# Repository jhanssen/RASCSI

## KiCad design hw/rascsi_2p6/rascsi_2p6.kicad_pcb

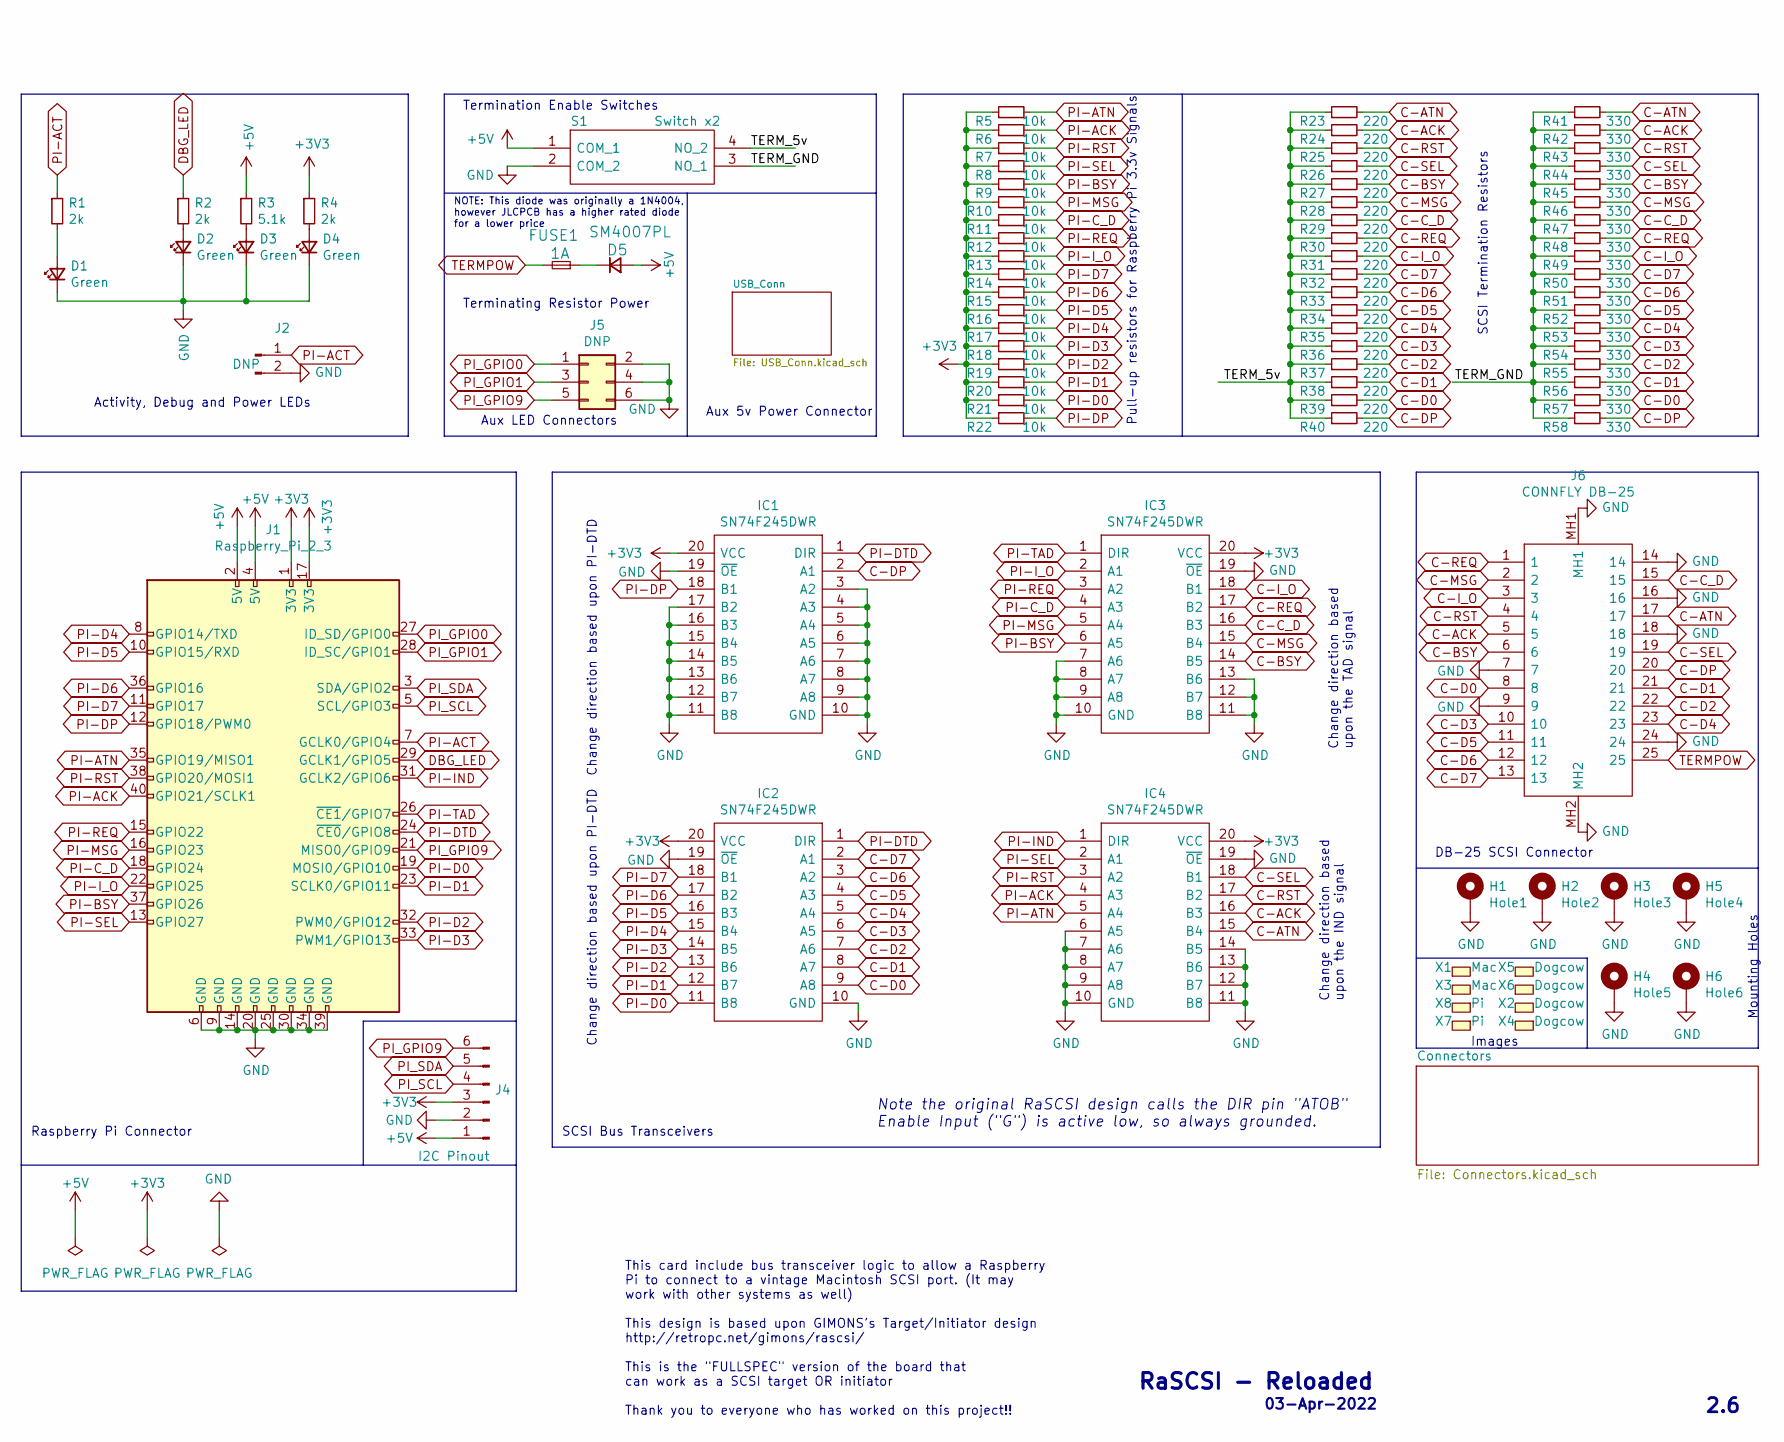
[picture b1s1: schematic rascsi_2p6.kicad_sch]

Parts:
D1, D2, D3, D4: Green; LED_0805_2012Metric; Manufacturer_Part_Number C2297; LCSC C2297
D5: SM4007PL; D_SOD-123F; Manufacturer_Part_Number SM4007PL; LCSC C64898
FUSE1: 1A; Fuse_1206_3216Metric; Manufacturer_Part_Number 12B1100B; LCSC C182974
H1: Hole1; MountingHole_2.7mm_M2.5_Pad_Via; Manufacturer_Part_Number DNP; LCSC DNP
H2: Hole2; MountingHole_2.7mm_M2.5_Pad_Via; Manufacturer_Part_Number DNP; LCSC DNP
H3: Hole3; MountingHole_2.7mm_M2.5_Pad_Via; Manufacturer_Part_Number DNP; LCSC DNP
H4: Hole5; MountingHole_2.7mm_M2.5_Pad_Via; Manufacturer_Part_Number DNP; LCSC DNP
H5: Hole4; MountingHole_2.7mm_M2.5_Pad_Via; Manufacturer_Part_Number DNP; LCSC DNP
H6: Hole6; MountingHole_2.7mm_M2.5_Pad_Via; Manufacturer_Part_Number DNP; LCSC DNP
IC1, IC2, IC3, IC4: SN74F245DWR; SOIC127P1030X265-20N; Manufacturer_Part_Number SN74F245DWR; LCSC C7165
J1: Raspberry_Pi_2_3; PinSocket_2x20_P2.54mm_Vertical; Manufacturer_Part_Number C50982; LCSC C50982
J2: DNP; PinHeader_1x02_P2.54mm_Horizontal; Manufacturer_Part_Number DNP; LCSC DNP
J4: I2C Pinout; PinSocket_1x06_P2.54mm_Vertical; Manufacturer_Part_Number C40877; LCSC C40877
J5: DNP; PinHeader_2x03_P2.54mm_Vertical; Manufacturer_Part_Number DNP; LCSC DNP
J6: CONNFLY DB-25; L717SDB25PA4CH4F; Manufacturer_Part_Number DS1037-25FNAKT74-0CC; LCSC C77838
R1, R2, R4: 2k; R_0402_1005Metric; Manufacturer_Part_Number 0402WGF2001TCE; LCSC C4109
R3: 5.1k; R_0402_1005Metric; Manufacturer_Part_Number 0402WGF5101TCE; LCSC C25905
R5, R6, R7, R8, R9, R10, R11, R12, R13, R14, R15, R16, R17, R18, R19, R20, R21, R22: 10k; R_0402_1005Metric; Manufacturer_Part_Number 0402WGF1002TCE; LCSC C25744
R23, R24, R25, R26, R27, R28, R29, R30, R31, R32, R33, R34, R35, R36, R37, R38, R39, R40: 220; R_0805_2012Metric; Manufacturer_Part_Number 0805W8F2200T5E; LCSC C17557
R41, R42, R43, R44, R45, R46, R47, R48, R49, R50, R51, R52, R53, R54, R55, R56, R57, R58: 330; R_0805_2012Metric; Manufacturer_Part_Number 0805W8F3300T5E; LCSC C17630
S1: Switch x2; SOIC127P812X230-4N; Manufacturer_Part_Number DSHP02TSGET; LCSC C40735
X1, X3: Mac; mac_happy_small; Manufacturer_Part_Number N/A; LCSC N/A
X2, X4, X5, X6: Dogcow; dogcow; Manufacturer_Part_Number N/A; LCSC N/A
X7: Pi; pi_logo; Manufacturer_Part_Number N/A; LCSC N/A
X8: Pi; scsi_logo; Manufacturer_Part_Number N/A; LCSC N/A

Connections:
+3V3: IC1.20 (VCC), IC2.20 (VCC), IC3.20 (VCC), IC4.20 (VCC), J1.1 (3V3), J1.17 (3V3), J4.3, R4.1, R5.1, R6.1, R7.1, R8.1, R9.1, R10.1, R11.1, R12.1, R13.1, R14.1, R15.1, R16.1, R17.1, R18.1, R19.1, R20.1, R21.1, R22.1
+5V: D5.2 (A), J1.2 (5V), J1.4 (5V), J4.1, R3.1, S1.1 (COM_1); also elsewhere on the board
/TERM_5v: R23.1, R24.1, R25.1, R26.1, R27.1, R28.1, R29.1, R30.1, R31.1, R32.1, R33.1, R34.1, R35.1, R36.1, R37.1, R38.1, R39.1, R40.1, S1.4 (NO_2)
/TERM_GND: R41.1, R42.1, R43.1, R44.1, R45.1, R46.1, R47.1, R48.1, R49.1, R50.1, R51.1, R52.1, R53.1, R54.1, R55.1, R56.1, R57.1, R58.1, S1.3 (NO_1)
C-ACK: IC4.16 (B3), J6.5, R24.2, R42.2; also elsewhere on the board
C-ATN: IC4.15 (B4), J6.17, R23.2, R41.2; also elsewhere on the board
C-BSY: IC3.14 (B5), J6.6, R27.2, R45.2; also elsewhere on the board
C-C_D: IC3.16 (B3), J6.15, R29.2, R47.2; also elsewhere on the board
C-D0: IC2.9 (A8), J6.8, R39.2, R57.2; also elsewhere on the board
C-D1: IC2.8 (A7), J6.21, R38.2, R56.2; also elsewhere on the board
C-D2: IC2.7 (A6), J6.22, R37.2, R55.2; also elsewhere on the board
C-D3: IC2.6 (A5), J6.10, R36.2, R54.2; also elsewhere on the board
C-D4: IC2.5 (A4), J6.23, R35.2, R53.2; also elsewhere on the board
C-D5: IC2.4 (A3), J6.11, R34.2, R52.2; also elsewhere on the board
C-D6: IC2.3 (A2), J6.12, R33.2, R51.2; also elsewhere on the board
C-D7: IC2.2 (A1), J6.13, R32.2, R50.2; also elsewhere on the board
C-DP: IC1.2 (A1), J6.20, R40.2, R58.2; also elsewhere on the board
C-I_O: IC3.18 (B1), J6.3, R31.2, R49.2; also elsewhere on the board
C-MSG: IC3.15 (B4), J6.2, R28.2, R46.2; also elsewhere on the board
C-REQ: IC3.17 (B2), J6.1, R30.2, R48.2; also elsewhere on the board
C-RST: IC4.17 (B2), J6.4, R25.2, R43.2; also elsewhere on the board
C-SEL: IC4.18 (B1), J6.19, R26.2, R44.2; also elsewhere on the board
DBG_LED: J1.29 (GCLK1/GPIO5), R2.1
GND: D1.1 (K), D2.1 (K), D3.1 (K), D4.1 (K), H1.1, H2.1, H3.1, H4.1, H5.1, H6.1, IC1.3 (A2), IC1.4 (A3), IC1.5 (A4), IC1.6 (A5), IC1.7 (A6), IC1.8 (A7), IC1.9 (A8), IC1.10 (GND), IC1.11 (B8), IC1.12 (B7), IC1.13 (B6), IC1.14 (B5), IC1.15 (B4), IC1.16 (B3), IC1.17 (B2), IC1.19 (~OE), IC2.10 (GND), IC2.19 (~OE), IC3.7 (A6), IC3.8 (A7), IC3.9 (A8), IC3.10 (GND), IC3.11 (B8), IC3.12 (B7), IC3.13 (B6), IC3.19 (~OE), IC4.6 (A5), IC4.7 (A6), IC4.8 (A7), IC4.9 (A8), IC4.10 (GND), IC4.11 (B8), IC4.12 (B7), IC4.13 (B6), IC4.14 (B5), IC4.19 (~OE), J1.6 (GND), J1.9 (GND), J1.14 (GND), J1.20 (GND), J1.25 (GND), J1.30 (GND), J1.34 (GND), J1.39 (GND), J2.2, J4.2, J5.2, J5.4, J5.6, J6.7, J6.9, J6.14, J6.16, J6.18, J6.24, J6.MH1, J6.MH2, S1.2 (COM_2); also elsewhere on the board
unnamed: D1.2 (A), R1.2
unnamed: D2.2 (A), R2.2
unnamed: D3.2 (A), R3.2
unnamed: D4.2 (A), R4.2
unnamed: D5.1 (K), FUSE1.1
PI-ACK: IC4.4 (A3), J1.40 (GPIO21/SCLK1), R6.2
PI-ACT: J1.7 (GCLK0/GPIO4), J2.1, R1.1; also elsewhere on the board
PI-ATN: IC4.5 (A4), J1.35 (GPIO19/MISO1), R5.2
PI-BSY: IC3.6 (A5), J1.37 (GPIO26), R9.2
PI-C_D: IC3.4 (A3), J1.18 (GPIO24), R11.2
PI-D0: IC2.11 (B8), J1.19 (MOSI0/GPIO10), R21.2
PI-D1: IC2.12 (B7), J1.23 (SCLK0/GPIO11), R20.2
PI-D2: IC2.13 (B6), J1.32 (PWM0/GPIO12), R19.2
PI-D3: IC2.14 (B5), J1.33 (PWM1/GPIO13), R18.2
PI-D4: IC2.15 (B4), J1.8 (GPIO14/TXD), R17.2
PI-D5: IC2.16 (B3), J1.10 (GPIO15/RXD), R16.2
PI-D6: IC2.17 (B2), J1.36 (GPIO16), R15.2
PI-D7: IC2.18 (B1), J1.11 (GPIO17), R14.2
PI-DP: IC1.18 (B1), J1.12 (GPIO18/PWM0), R22.2
PI-DTD: IC1.1 (DIR), IC2.1 (DIR), J1.24 (~CE0/GPIO8)
PI-IND: IC4.1 (DIR), J1.31 (GCLK2/GPIO6)
PI-I_O: IC3.2 (A1), J1.22 (GPIO25), R13.2
PI-MSG: IC3.5 (A4), J1.16 (GPIO23), R10.2
PI-REQ: IC3.3 (A2), J1.15 (GPIO22), R12.2
PI-RST: IC4.3 (A2), J1.38 (GPIO20/MOSI1), R7.2
PI-SEL: IC4.2 (A1), J1.13 (GPIO27), R8.2
PI-TAD: IC3.1 (DIR), J1.26 (~CE1/GPIO7)
PI_GPIO0: J1.27 (ID_SD/GPIO0), J5.1
PI_GPIO1: J1.28 (ID_SC/GPIO1), J5.3
PI_GPIO9: J1.21 (MISO0/GPIO9), J4.6, J5.5
PI_SCL: J1.5 (SCL/GPIO3), J4.4
PI_SDA: J1.3 (SDA/GPIO2), J4.5
TERMPOW: FUSE1.2, J6.25; also elsewhere on the board

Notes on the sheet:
Images
RaSCSI - Reloaded
2.6
Raspberry Pi Connector
Change direction based upon the TAD signal
Terminating Resistor Power
Mounting Holes
03-Apr-2022
DB-25 SCSI Connector
SCSI Termination Resistors
Pull-up resistors for Raspberry Pi 3.3v Signals
Change direction based upon the IND signal
NOTE: This diode was originally a 1N4004, however JLCPCB has a higher rated diode for a lower price
Change direction based upon PI-DTD
Note the original RaSCSI design calls the DIR pin "ATOB" Enable Input ("G") is active low, so always grounded.
Activity, Debug and Power LEDs
Termination Enable Switches
This card include bus transceiver logic to allow a Raspberry Pi to connect to a vintage Macintosh SCSI port. (It may work with other systems as well) This design is based upon GIMONS's Target/Initiator design http://retropc.net/gimons/rascsi/ This is the "FULLSPEC" version of the board that can wor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
Aux 5v Power Connector
SCSI Bus Transceivers
Aux LED Connectors

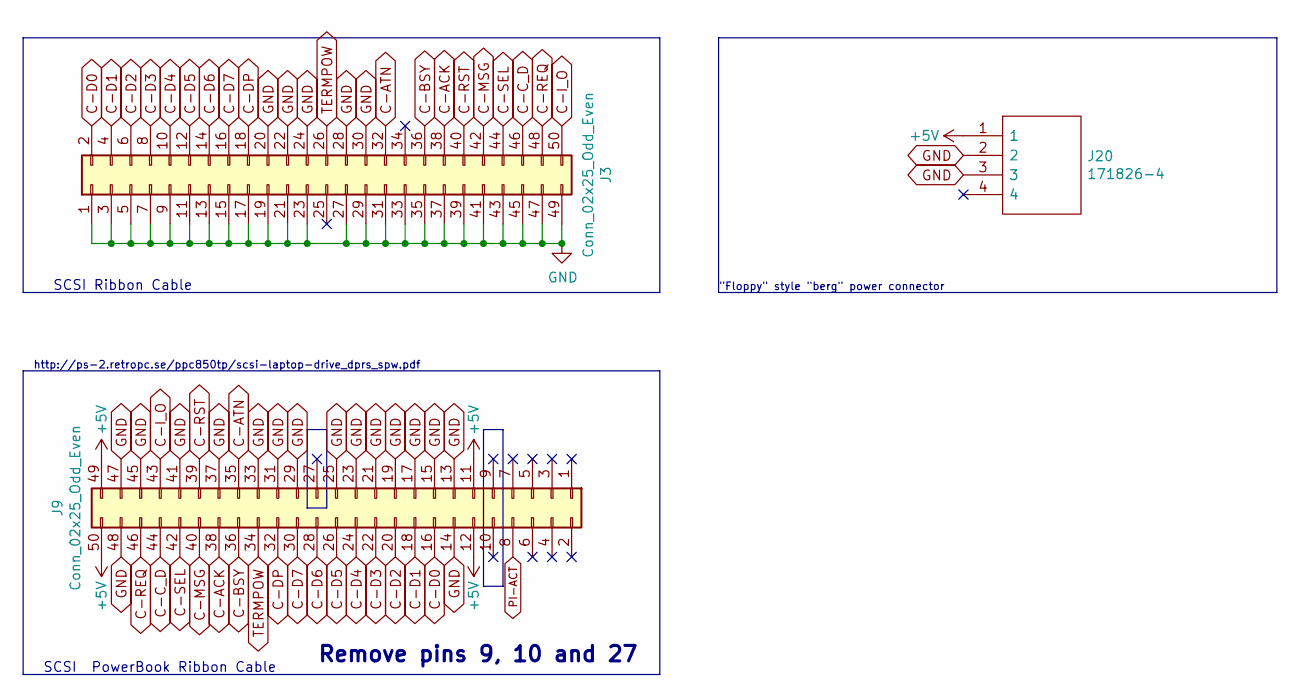
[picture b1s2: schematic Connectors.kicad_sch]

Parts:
J3: Conn_02x25_Odd_Even; PinHeader_2x25_P2.54mm_Vertical; Manufacturer_Part_Number C30006; LCSC C30006
J9: Conn_02x25_Odd_Even; PinHeader_2x25_P2.00mm_Horizontal; Manufacturer_Part_Number C3407; LCSC C3407
J20: 171826-4; PinHeader_1x04_P2.54mm_Vertical; Manufacturer_Part_Number 171826-4

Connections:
+5V: J9.11, J9.12, J9.49, J9.50, J20.1; also elsewhere on the board
C-ACK: J3.38, J9.38; also elsewhere on the board
C-ATN: J3.32, J9.35; also elsewhere on the board
C-BSY: J3.36, J9.36; also elsewhere on the board
C-C_D: J3.46, J9.44; also elsewhere on the board
C-D0: J3.2, J9.16; also elsewhere on the board
C-D1: J3.4, J9.18; also elsewhere on the board
C-D2: J3.6, J9.20; also elsewhere on the board
C-D3: J3.8, J9.22; also elsewhere on the board
C-D4: J3.10, J9.24; also elsewhere on the board
C-D5: J3.12, J9.26; also elsewhere on the board
C-D6: J3.14, J9.28; also elsewhere on the board
C-D7: J3.16, J9.30; also elsewhere on the board
C-DP: J3.18, J9.32; also elsewhere on the board
C-I_O: J3.50, J9.43; also elsewhere on the board
C-MSG: J3.42, J9.40; also elsewhere on the board
C-REQ: J3.48, J9.46; also elsewhere on the board
C-RST: J3.40, J9.39; also elsewhere on the board
C-SEL: J3.44, J9.42; also elsewhere on the board
GND: J3.1, J3.3, J3.5, J3.7, J3.9, J3.11, J3.13, J3.15, J3.17, J3.19, J3.20, J3.21, J3.22, J3.23, J3.24, J3.27, J3.28, J3.29, J3.30, J3.31, J3.33, J3.35, J3.37, J3.39, J3.41, J3.43, J3.45, J3.47, J3.49, J9.13, J9.14, J9.15, J9.17, J9.19, J9.21, J9.23, J9.25, J9.29, J9.31, J9.33, J9.37, J9.41, J9.45, J9.47, J9.48, J20.2, J20.3; also elsewhere on the board
PI-ACT: J9.8; also elsewhere on the board
TERMPOW: J3.26, J9.34; also elsewhere on the board

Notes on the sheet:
Remove pins 9, 10 and 27
SCSI Ribbon Cable
"Floppy" style "berg" power connector
http://ps-2.retropc.se/ppc850tp/scsi-laptop-drive_dprs_spw.pdf
SCSI PowerBook Ribbon Cable

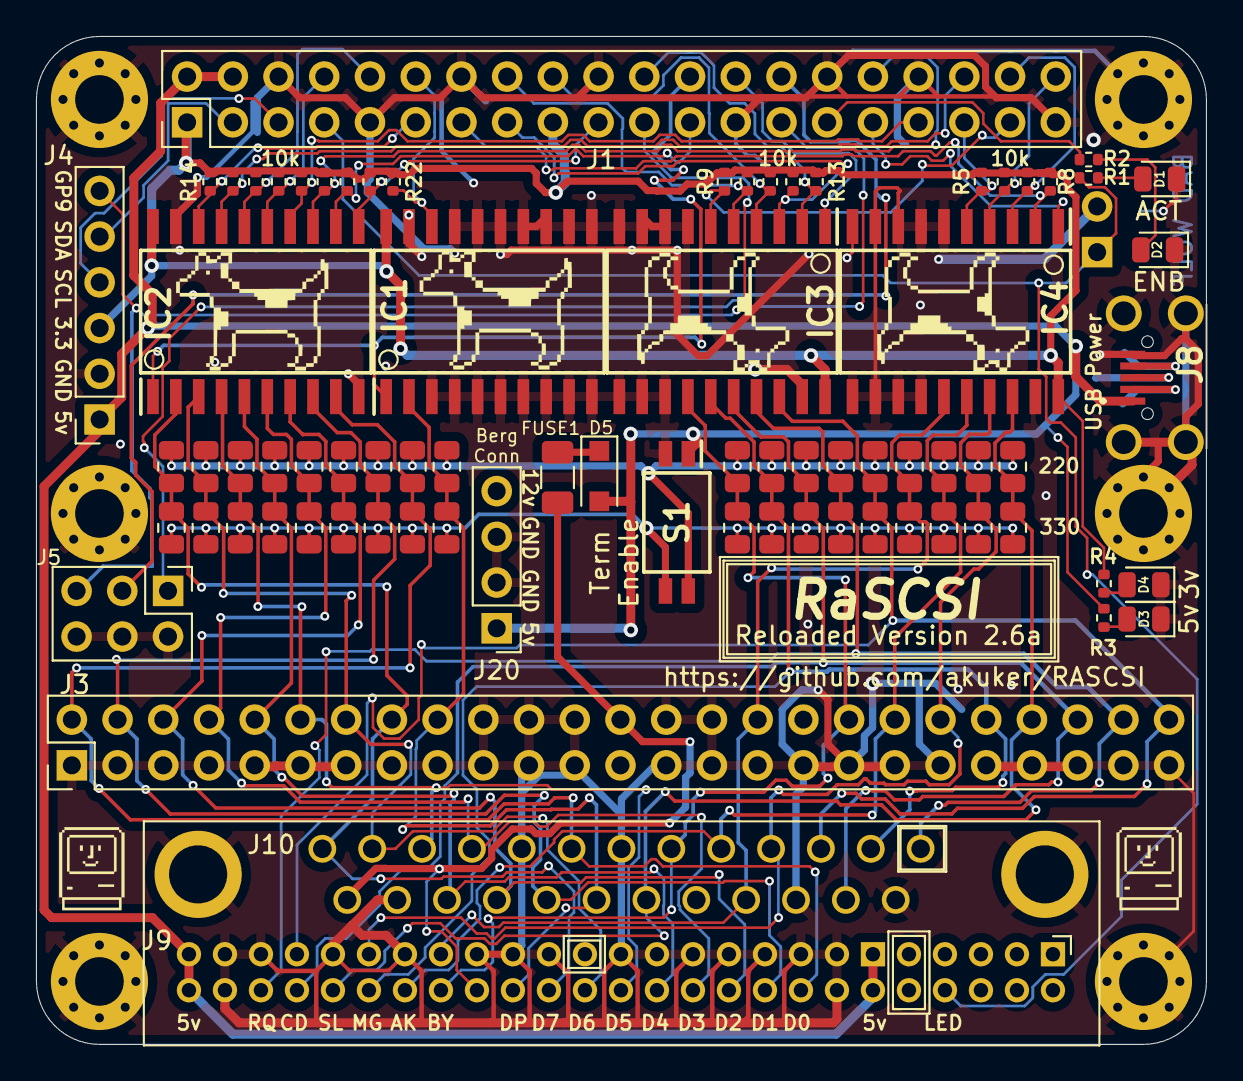
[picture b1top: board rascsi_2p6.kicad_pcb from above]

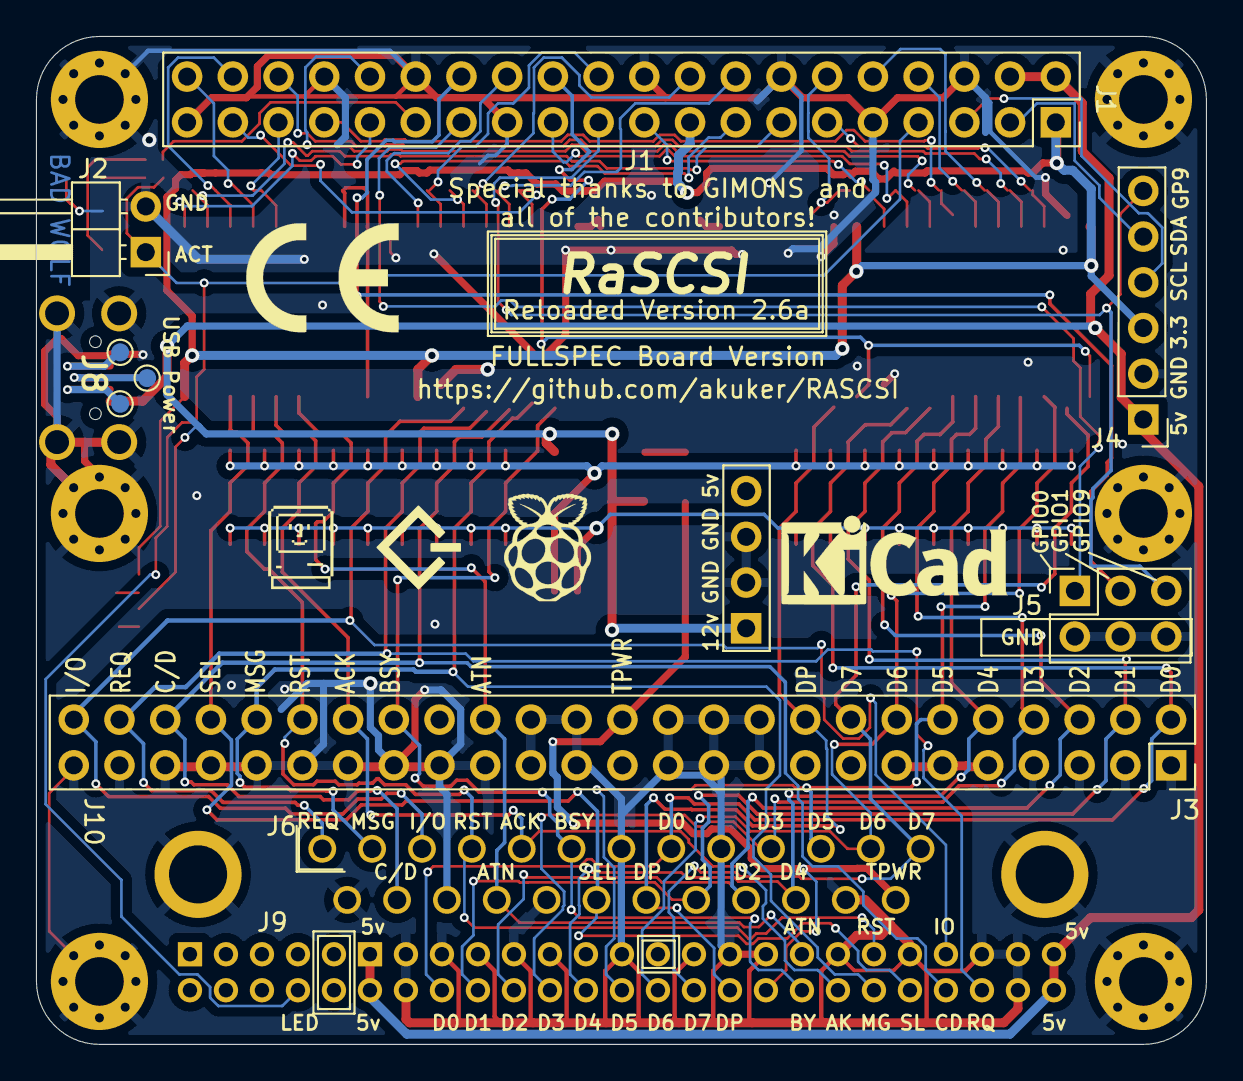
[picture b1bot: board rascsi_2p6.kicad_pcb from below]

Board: 2 copper layers, 65.0 x 56.0 mm, 95 parts (9 on the bottom side), 60 nets.

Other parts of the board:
J8: USB_B_Micro; U254051N4BH806
TP1, TP2, TP3: TestPoint; TestPoint_Pad_D1.0mm

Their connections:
+5V: J8.1; also elsewhere on the board
GND: J8.5, J8.MH1, J8.MH2, J8.MH3, J8.MH4; also elsewhere on the board
USB_Pin_2: J8.2, TP3.1
USB_Pin_3: J8.3, TP2.1
USB_Pin_4: J8.4, TP1.1

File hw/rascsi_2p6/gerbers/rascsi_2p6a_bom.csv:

Comment,Designator,Footprint,LCSC
"Green","D1,D2,D3,D4","LED_SMD:LED_0805_2012Metric","C2297"
"SM4007PL","D5","Diode_SMD:D_SOD-123F","C64898"
"1A","FUSE1","Fuse:Fuse_1206_3216Metric","C182974"
"Hole1","H1","MountingHole:MountingHole_2.7mm_M2.5_Pad_Via","DNP"
"Hole2","H2","MountingHole:MountingHole_2.7mm_M2.5_Pad_Via","DNP"
"Hole3","H3","MountingHole:MountingHole_2.7mm_M2.5_Pad_Via","DNP"
"Hole5","H4","MountingHole:MountingHole_2.7mm_M2.5_Pad_Via","DNP"
"Hole4","H5","MountingHole:MountingHole_2.7mm_M2.5_Pad_Via","DNP"
"Hole6","H6","MountingHole:MountingHole_2.7mm_M2.5_Pad_Via","DNP"
"SN74F245DWR","IC1,IC2,IC3,IC4","SamacSys_Parts:SOIC127P1030X265-20N","C7165"
"Raspberry_Pi_2_3","J1","Connector_PinSocket_2.54mm:PinSocket_2x20_P2.54mm_Vertical","C50982"
"DNP","J2","Connector_PinHeader_2.54mm:PinHeader_1x02_P2.54mm_Horizontal","DNP"
"171826-4","J20","Connector_PinHeader_2.54mm:PinHeader_1x04_P2.54mm_Vertical",""
"Conn_02x25_Odd_Even","J3","Connector_PinHeader_2.54mm:PinHeader_2x25_P2.54mm_Vertical","C30006"
"I2C Pinout","J4","Connector_PinSocket_2.54mm:PinSocket_1x06_P2.54mm_Vertical","C40877"
"DNP","J5","Connector_PinHeader_2.54mm:PinHeader_2x03_P2.54mm_Vertical","DNP"
"CONNFLY DB-25","J6","SamacSys_Parts:L717SDB25PA4CH4F","C77838"
"USB_B_Micro","J8","SamacSys_Parts:U254051N4BH806","C319170"
"Conn_02x25_Odd_Even","J9","Connector_PinHeader_2.00mm:PinHeader_2x25_P2.00mm_Horizontal","C3407"
"2k","R1,R2,R4","Resistor_SMD:R_0402_1005Metric","C4109"
"220","R23,R24,R25,R26,R27,R28,R29,R30,R31,R32,R33,R34,R35,R36,R37,R38,R39,R40","Resistor_SMD:R_0805_2012Metric","C17557"
"5.1k","R3","Resistor_SMD:R_0402_1005Metric","C25905"
"330","R41,R42,R43,R44,R45,R46,R47,R48,R49,R50,R51,R52,R53,R54,R55,R56,R57,R58","Resistor_SMD:R_0805_2012Metric","C17630"
"10k","R5,R6,R7,R8,R9,R10,R11,R12,R13,R14,R15,R16,R17,R18,R19,R20,R21,R22","Resistor_SMD:R_0402_1005Metric","C25744"
"Switch x2","S1","rascsi_din:SOIC127P812X230-4N","C40735"
"TestPoint","TP1,TP2,TP3","TestPoint:TestPoint_Pad_D1.0mm","N/A"
"Mac","X1,X3","SamacSys_Parts:mac_happy_small","N/A"
"Dogcow","X2,X4,X5,X6","SamacSys_Parts:dogcow","N/A"
"Pi","X7","SamacSys_Parts:pi_logo","N/A"
"Pi","X8","SamacSys_Parts:scsi_logo","N/A"

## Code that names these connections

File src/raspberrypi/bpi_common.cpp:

/*
Copyright (c) 2013-2014 Ben Croston

Permission is hereby granted, free of charge, to any person obtaining a copy of
this software and associated documentation files (the "Software"), to deal in
the Software without restriction, including without limitation the rights to
use, copy, modify, merge, publish, distribute, sublicense, and/or sell copies
of the Software, and to permit persons to whom the Software is furnished to do
so, subject to the following conditions:

The above copyright notice and this permission notice shall be included in all
copies or substantial portions of the Software.

THE SOFTWARE IS PROVIDED "AS IS", WITHOUT WARRANTY OF ANY KIND, EXPRESS OR
IMPLIED, INCLUDING BUT NOT LIMITED TO THE WARRANTIES OF MERCHANTABILITY,
FITNESS FOR A PARTICULAR PURPOSE AND NONINFRINGEMENT. IN NO EVENT SHALL THE
AUTHORS OR COPYRIGHT HOLDERS BE LIABLE FOR ANY CLAIM, DAMAGES OR OTHER
LIABILITY, WHETHER IN AN ACTION OF CONTRACT, TORT OR OTHERWISE, ARISING FROM,
OUT OF OR IN CONNECTION WITH THE SOFTWARE OR THE USE OR OTHER DEALINGS IN THE
SOFTWARE.
*/

#include "bpi_c_gpio.h"
#include "bpi_common.h"
#include <stdio.h>

int bpi_common::gpio_mode = MODE_UNKNOWN;

const int bpi_common::physToGpio_BP [64] =		//BOARD MODE
{
	-1, // 0
	-1, -1, //1, 2
	53, -1, //3, 4
	52, -1, //5, 6
	259, 224, //7, 8  (8--228)
	-1, 225, //9, 10
	275, 226, //11, 12
	274, -1, //13, 14
	273, 244, //15, 16
	-1, 245, //17, 18
	268, -1, //19, 20
	269, 272, //21, 22
	267, 266, //23, 24
	-1, 270, //25, 26
	
	257, 256, //27, 28
	35, -1, //29, 30
	277, 276, //31, 32
	45, -1, //33, 34
	39, 38, //35, 36
	37, 44, //37, 38
	-1, 40, //39, 40
	-1, -1, -1, -1, -1, -1, -1, -1, -1, -1, -1, -1, -1, -1, -1, //41-> 55
	-1, -1, -1, -1, -1, -1, -1, -1 // 56-> 63
} ;

// TODO: In RPi.GPIO_BP, this is set dynamically.... 
const int (*bpi_common::pin_to_gpio)[64] = &bpi_common::physToGpio_BP;

const int bpi_common::pinTobcm_BP [64] =	//BCM MODE
{
	-1,-1, //map to BCM GPIO0,1
	53,52, //map to BCM GPIO2,3
	259,-1, //map to BCM GPIO4,5
	-1,270, //map to BCM GPIO6,7
	266,269, //map to BCM GPIO8,9
	268,267, //map to BCM GPIO10,11
	-1,-1, //map to BCM GPIO12,13
	224,225, //map to BCM GPIO14,15
	-1,275, //map to BCM GPIO16,17
	226,-1, //map to BCM GPIO18,19
	-1, -1, //map to BCM GPIO20,21
	273,244, //map to BCM GPIO22,23
	245,272, //map to BCM GPIO24,25
	-1, 274, //map to BCM GPIO26,27
	
	-1,-1, -1, -1, -1, -1, -1, -1, -1, -1, -1, -1, -1, -1, -1, -1, // 29... 44
	-1, -1, -1, -1, -1, -1, -1, -1, -1, -1, -1, -1, -1, -1, -1, -1, //45... 60
	-1, -1, -1, -1 // ...63
} ;
const int bpi_common::physToGpioR3 [64] =//head num map to BCMpin
{
	-1, // 0
	-1, -1, // 1, 2
	2, -1,
	3, -1,
	4, 14,
	-1, 15,
	17, 18,
	27, -1,
	22, 23,
	-1, 24,
	10, -1,
	9, 25,
	11, 8,
	-1, 7, // 25, 26
	
	0, 1, //27, 28
	5, -1, //29, 30
	6, 12, //31, 32
	13, -1, //33, 34
	19, 16, //35, 36
	26, 20, //37, 38
	-1, 21, //39, 40
	// Padding:
	-1, -1, -1, -1, -1, -1, -1, -1, -1, -1, -1, -1, -1, -1, -1, -1, // ... 56
	-1, -1, -1, -1, -1, -1, -1, // ... 63
} ;

int bpi_common::setup_error = 0;
int bpi_common::module_setup = 0;
int bpi_common::revision = -1;

extern int f_a20;

int bpi_common::check_gpio_priv(void)
{
    // check module has been imported cleanly
    if (setup_error)
    {
        printf("Module not imported correctly!");
        return 1;
    }

    // check mmap setup has worked
    if (!module_setup)
    {
        printf("No access to /dev/mem.  Try running as root!");
        return 2;
    }
    return 0;
}

int bpi_common::is_valid_raw_port(int channel)
{
    if (channel >=   0 && channel <  18) return 1; // PA
    if (channel >=  32 && channel <  56) return 2; // PB
    if (channel >=  64 && channel <  89) return 3; // PC
    if (channel >=  96 && channel < 124) return 4; // PD
    if (channel >= 128 && channel < 140) return 5; // PE
    if (channel >= 160 && channel < 166) return 6; // PF
    if (channel >= 192 && channel < 204) return 7; // PG
    if (channel >= 224 && channel < 252) return 8; // PH
    if (channel >= 256 && channel < 278) return 9; // PI
    return 0;
}

int bpi_common::get_gpio_number(int channel, unsigned int *gpio)
{


    // check channel number is in range
    if ( (gpio_mode == BCM && (channel < 0 || channel > 64))
      || (gpio_mode == BOARD && (channel < 1 || channel > 64)) )
    {
        printf( "The channel sent is invalid on a Banana Pi");
        return 4;
    }

    // convert channel to gpio
    if (gpio_mode == BOARD)
    {
    if (*(*pin_to_gpio+channel) == -1)
        {
            printf("The channel sent is invalid on a Banana Pi");
            return 5;
        } else {
            *gpio = *(*pin_to_gpio+channel);	//pin_to_gpio is initialized in py_gpio.c, the last several lines
        }
    }
    else if (gpio_mode == BCM)
    {
          *gpio = *(pinTobcm_BP + channel); 
    }
    else if (gpio_mode == MODE_RAW)
    {
        if (!is_valid_raw_port(channel))
        {
            printf( "The channel sent does not exist");
            return 5;
        }
        *gpio = channel;
    } else {
        // setmode() has not been run
        printf( "Please set pin numbering mode using GPIO.setmode(GPIO.BOARD) or GPIO.setmode(GPIO.BCM) or GPIO.setmode(GPIO.RAW)");
        return 3;
    }
    
	if(lemakerDebug)
		printf("GPIO = %d\n", *gpio);
    return 0;
}

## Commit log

2022-02-13 sn74ls245 test
2022-02-27 need to specifically call out libprotobuf-dev for Armbian
2022-04-04 Increased resistor size & added ctrl board interrupt
2022-04-07 Fixed orientation of .POS files
2022-04-15 updates for bpi m2 berry
2022-04-17 Updated to use 3.3v vcc instead of 5v
2022-04-17 fix error about missing background drawing
2022-04-23 Intermediate
2022-07-02 add bin/cue parser from https://github.com/jhanssen/bincue
2022-07-02 add a simple file descriptor read notifier
2022-07-02 comment out log warns for mode select
2022-07-02 add new scsicd command codes
2022-07-02 add some disk logging
2022-07-02 add a way to set the total disk blocks (in case of multiple bin files in a cue sheet) and the data image offset
2022-07-02 might not be possible to open disk images with O_DIRECT
2022-07-02 add a way to get a Fileio handle
2022-07-02 add accessors for Dir and FileExt
2022-07-02 add new scsicd functionality
2022-07-02 forgot this
2022-07-03 bump bincue
